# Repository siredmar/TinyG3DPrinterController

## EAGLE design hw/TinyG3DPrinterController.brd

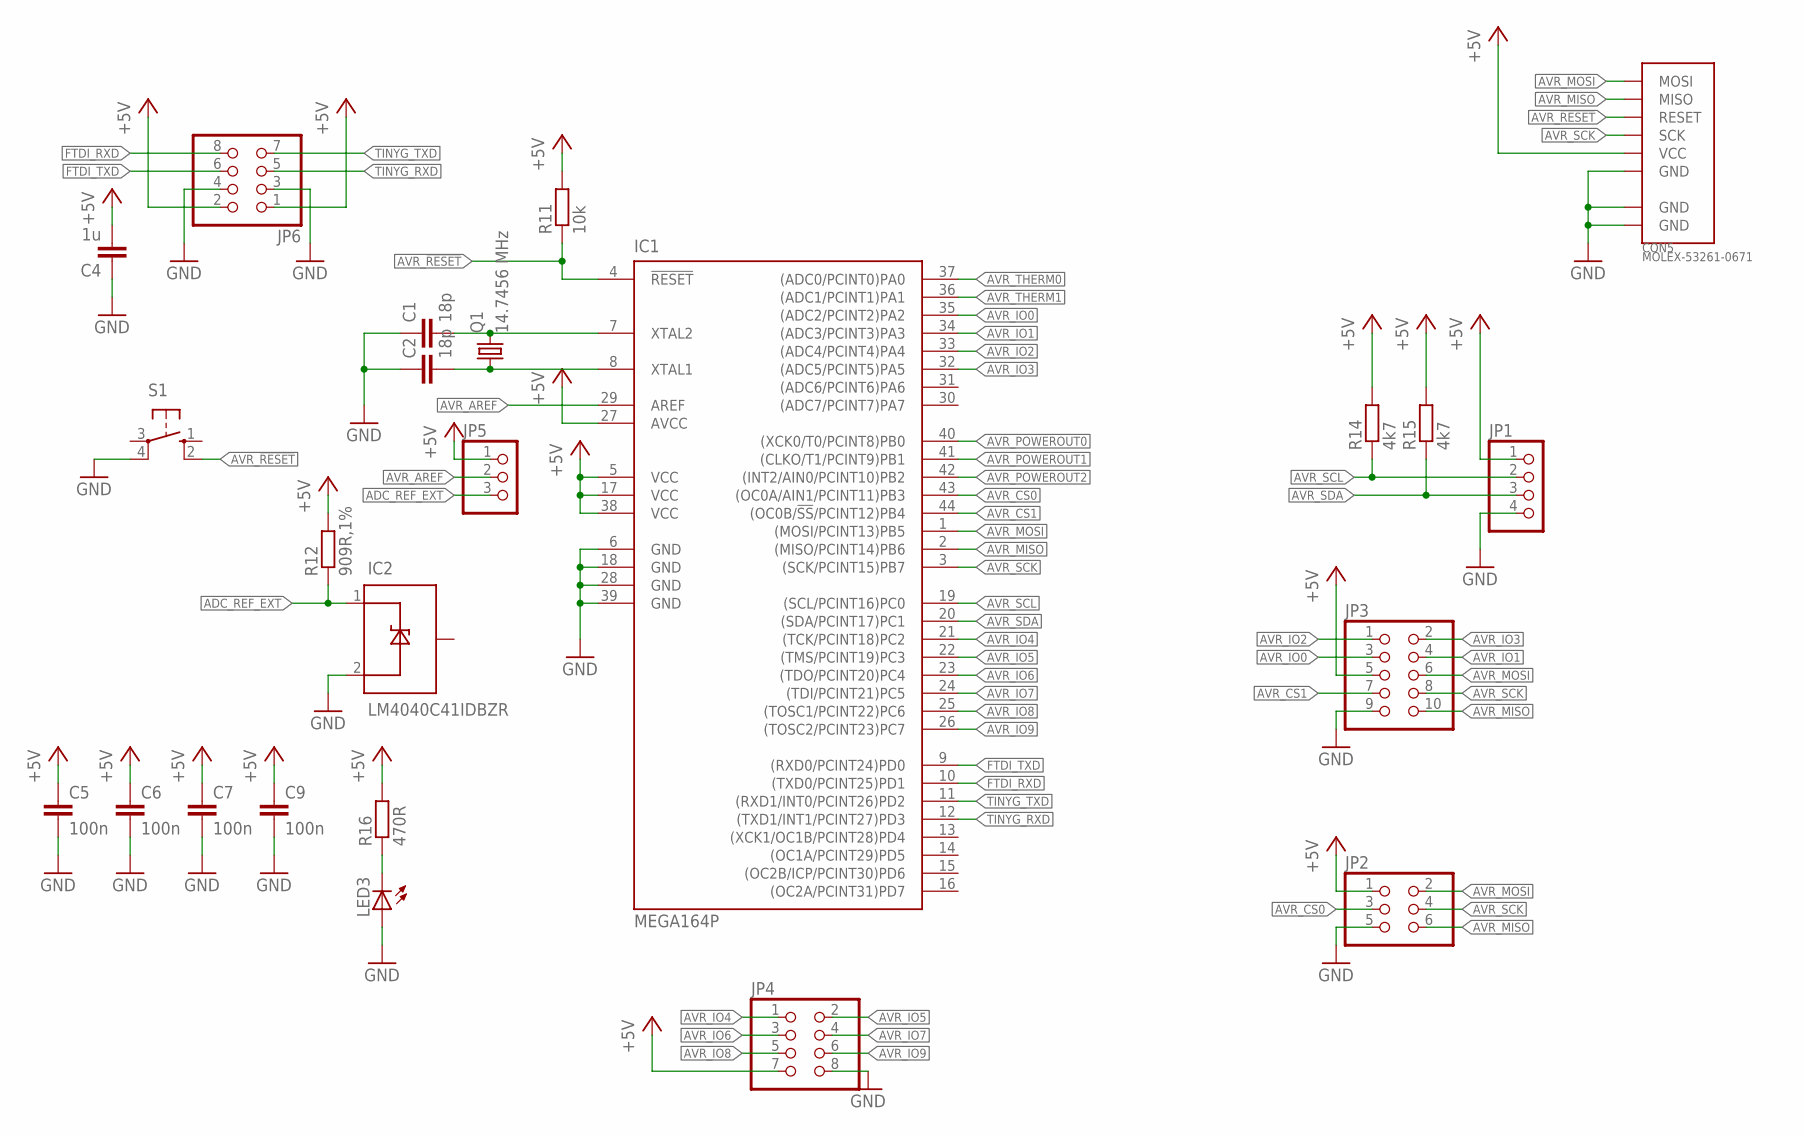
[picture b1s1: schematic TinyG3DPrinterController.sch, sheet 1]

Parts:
C1, C2: 18p; C0603K
C4: 1u; C1206K
C5, C6, C7, C9: 100n; C0603K
CON5: MOLEX-53261-0671
IC1: MEGA164P; TQFP44
IC2: LM4040C41IDBZR; SOT-23-3
JP1: PINHD-1X4; 1X04
JP2: PINHD-2X3; 2X03
JP3: PINHD-2X5; 2X05
JP4, JP6: PINHD-2X4; 2X04
JP5: PINHD-1X3; 1X03
LED3: LEDCHIP-LED0805; CHIP-LED0805
Q1: 14.7456 MHz; CRYSTAL_2P_5MMX3.2MM
R11: 10k; R0603
R12: 909R,1%; R0603
R14, R15: 4k7; R0603
R16: 470R; R0603
S1: 10-XX; B3F-10XX

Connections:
+5V: C4.2, C5.1, C6.1, C7.1, C9.1, CON5.5 (VCC), IC1.5 (VCC), IC1.17 (VCC), IC1.27 (AVCC), IC1.38 (VCC), JP1.1, JP2.1, JP3.5, JP4.7, JP5.1, JP6.1, JP6.2, R11.2, R12.2, R14.2, R15.2, R16.2; also elsewhere on the board
ADC_REF_EXT: IC2.1, JP5.3, R12.1
AVR_!RESET: CON5.3 (RESET), IC1.4 (!RESET), R11.1, S1.2 (S1)
AVR_AREF: IC1.29 (AREF), JP5.2
AVR_CS0: IC1.43 ((OC0A/AIN1/PCINT11)PB3), JP2.3
AVR_CS1: IC1.44 ((OC0B/!SS!/PCINT12)PB4), JP3.7
AVR_IO0: IC1.35 ((ADC2/PCINT2)PA2), JP3.3
AVR_IO1: IC1.34 ((ADC3/PCINT3)PA3), JP3.4
AVR_IO2: IC1.33 ((ADC4/PCINT4)PA4), JP3.1
AVR_IO3: IC1.32 ((ADC5/PCINT5)PA5), JP3.2
AVR_IO4: IC1.21 ((TCK/PCINT18)PC2), JP4.1
AVR_IO5: IC1.22 ((TMS/PCINT19)PC3), JP4.2
AVR_IO6: IC1.23 ((TDO/PCINT20)PC4), JP4.3
AVR_IO7: IC1.24 ((TDI/PCINT21)PC5), JP4.4
AVR_IO8: IC1.25 ((TOSC1/PCINT22)PC6), JP4.5
AVR_IO9: IC1.26 ((TOSC2/PCINT23)PC7), JP4.6
AVR_MISO: CON5.2 (MISO), IC1.2 ((MISO/PCINT14)PB6), JP2.6, JP3.10
AVR_MOSI: CON5.1 (MOSI), IC1.1 ((MOSI/PCINT13)PB5), JP2.2, JP3.6
AVR_POWEROUT0: IC1.40 ((XCK0/T0/PCINT8)PB0); also elsewhere on the board
AVR_POWEROUT1: IC1.41 ((CLKO/T1/PCINT9)PB1); also elsewhere on the board
AVR_POWEROUT2: IC1.42 ((INT2/AIN0/PCINT10)PB2); also elsewhere on the board
AVR_SCK: CON5.4 (SCK), IC1.3 ((SCK/PCINT15)PB7), JP2.4, JP3.8
AVR_SCL: IC1.19 ((SCL/PCINT16)PC0), JP1.2, R14.1
AVR_SDA: IC1.20 ((SDA/PCINT17)PC1), JP1.3, R15.1
AVR_THERM0: IC1.37 ((ADC0/PCINT0)PA0); also elsewhere on the board
AVR_THERM1: IC1.36 ((ADC1/PCINT1)PA1); also elsewhere on the board
FTDI_RXD: IC1.10 ((TXD0/PCINT25)PD1), JP6.8
FTDI_TXD: IC1.9 ((RXD0/PCINT24)PD0), JP6.6
GND: C1.1, C2.1, C4.1, C5.2, C6.2, C7.2, C9.2, CON5.6 (GND), CON5.GND@1 (GND), CON5.GND@2 (GND), IC1.6 (GND), IC1.18 (GND), IC1.28 (GND), IC1.39 (GND), IC2.2, JP1.4, JP2.5, JP3.9, JP4.8, JP6.3, JP6.4, LED3.A, S1.4 (P1); also elsewhere on the board
unnamed: C1.2, IC1.7 (XTAL2), Q1.P$2 (2)
unnamed: C2.2, IC1.8 (XTAL1), Q1.P$1 (1)
unnamed: LED3.C, R16.1
TINYG_RXD: IC1.12 ((TXD1/INT1/PCINT27)PD3), JP6.5
TINYG_TXD: IC1.11 ((RXD1/INT0/PCINT26)PD2), JP6.7

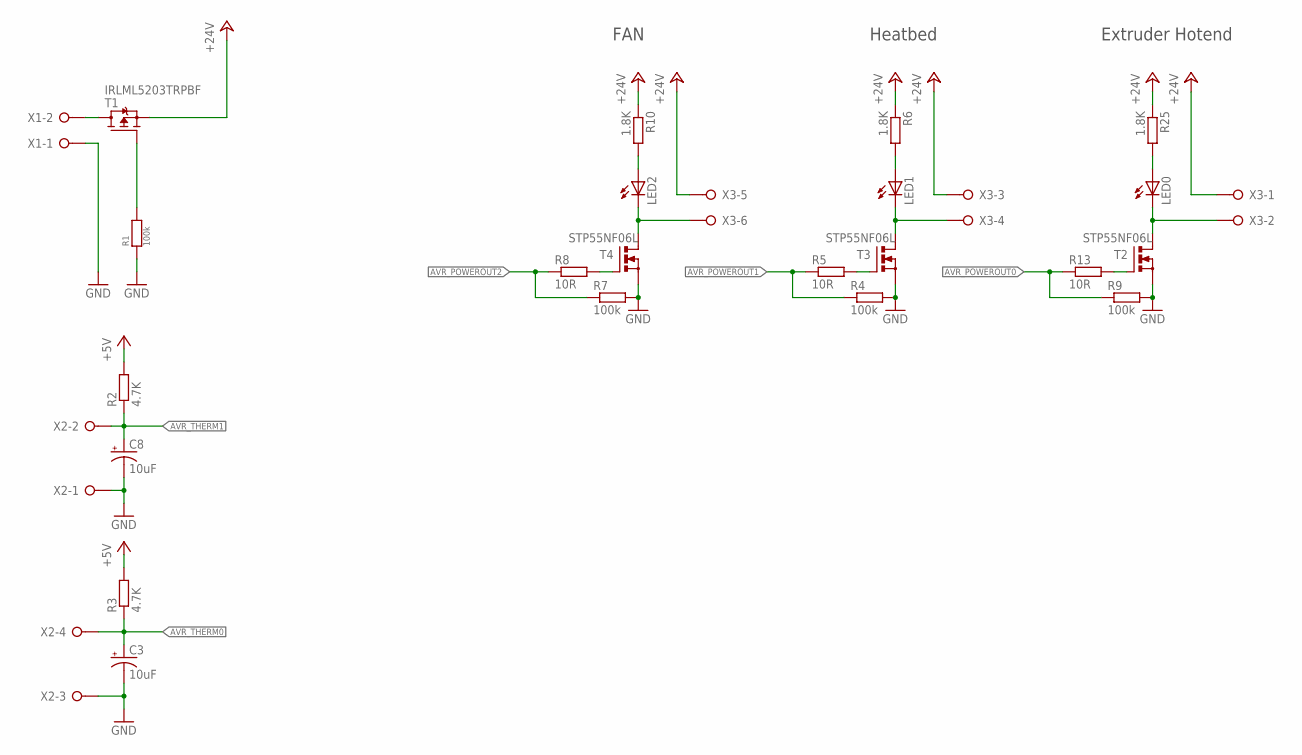
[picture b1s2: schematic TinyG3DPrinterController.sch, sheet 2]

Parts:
C3, C8: 10uF; 153CLV-0405
LED0, LED1, LED2: LEDCHIP-LED0805; CHIP-LED0805
R1, R4, R7, R9: 100k; R0603
R2, R3: 4.7K; R0603
R5, R8, R13: 10R; R0603
R6, R10, R25: 1.8K; R0603
T1: IRLML5203TRPBF; SOT23
T2, T3, T4: STP55NF06L; TO220BV
X1: W237-02P; W237-132
X2: W237-04P; W237-4P
X3: W237-06P; W237-6P

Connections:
+5V: R2.2, R3.2; also elsewhere on the board
+24V: R6.1, R10.1, R25.1, T1.2 (S), X3.1, X3.3, X3.5
AVR_POWEROUT0: R9.1, R13.1; also elsewhere on the board
AVR_POWEROUT1: R4.1, R5.1; also elsewhere on the board
AVR_POWEROUT2: R7.1, R8.1; also elsewhere on the board
AVR_THERM0: C3.+, R3.1, X2.4; also elsewhere on the board
AVR_THERM1: C8.+, R2.1, X2.2; also elsewhere on the board
GND: C3.-, C8.-, R1.1, R4.2, R7.2, R9.2, T2.S, T3.S, T4.S, X1.1, X2.1, X2.3; also elsewhere on the board
unnamed: R1.2, T1.1 (G)
unnamed: T1.3 (D), X1.2
unnamed: LED0.C, T2.D, X3.2
unnamed: R5.2, T3.G
unnamed: LED1.A, R6.2
unnamed: LED1.C, T3.D, X3.4
unnamed: R8.2, T4.G
unnamed: LED2.A, R10.2
unnamed: LED2.C, T4.D, X3.6
unnamed: R13.2, T2.G
unnamed: LED0.A, R25.2

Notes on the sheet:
Extruder Hotend
Heatbed
FAN

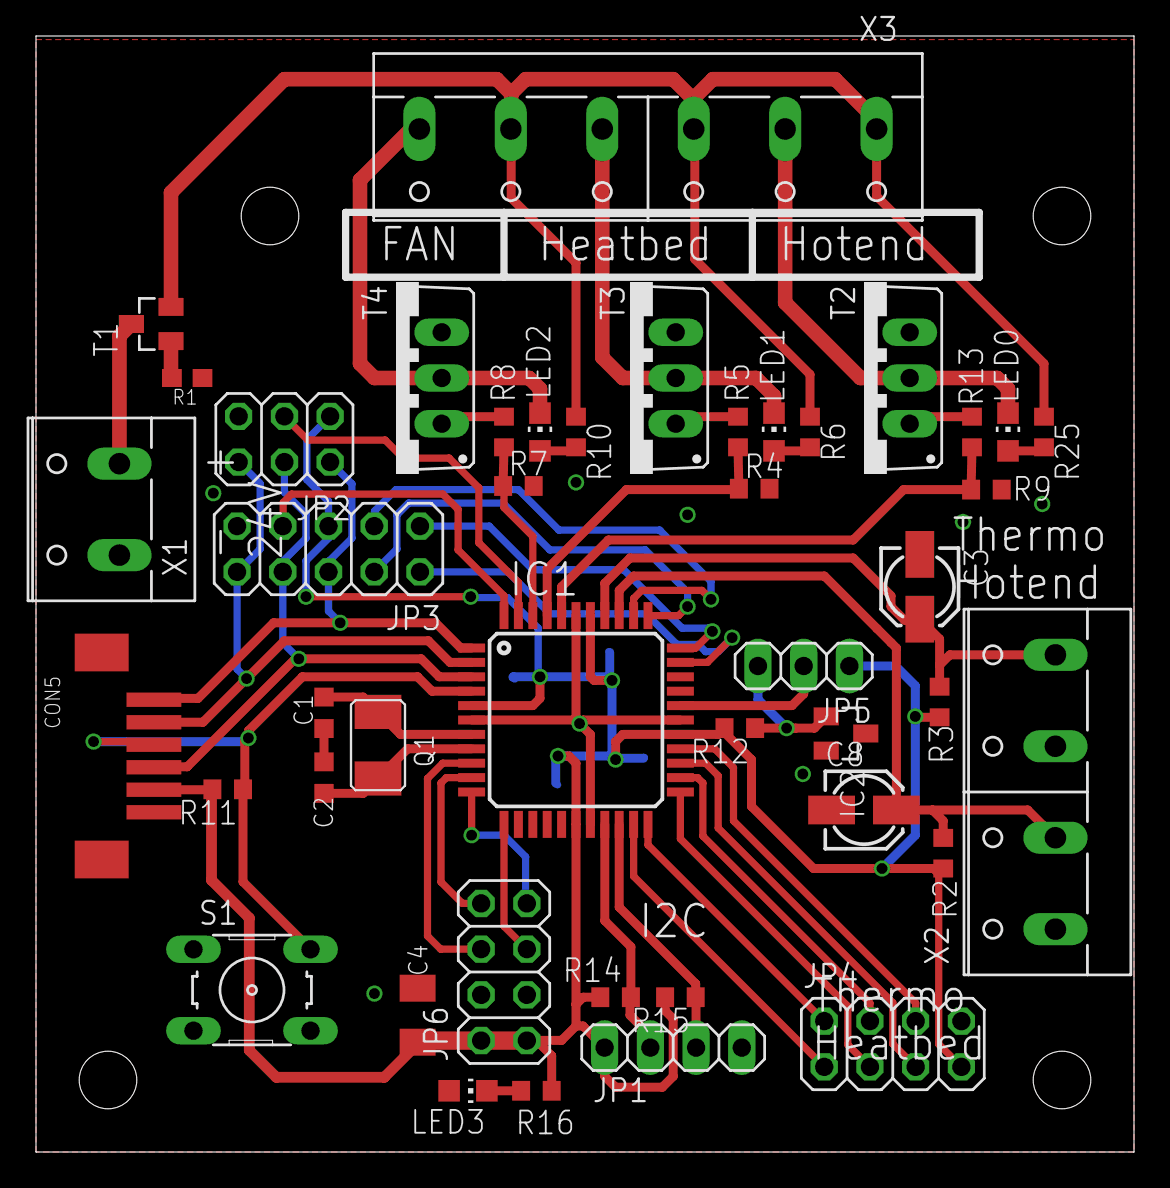
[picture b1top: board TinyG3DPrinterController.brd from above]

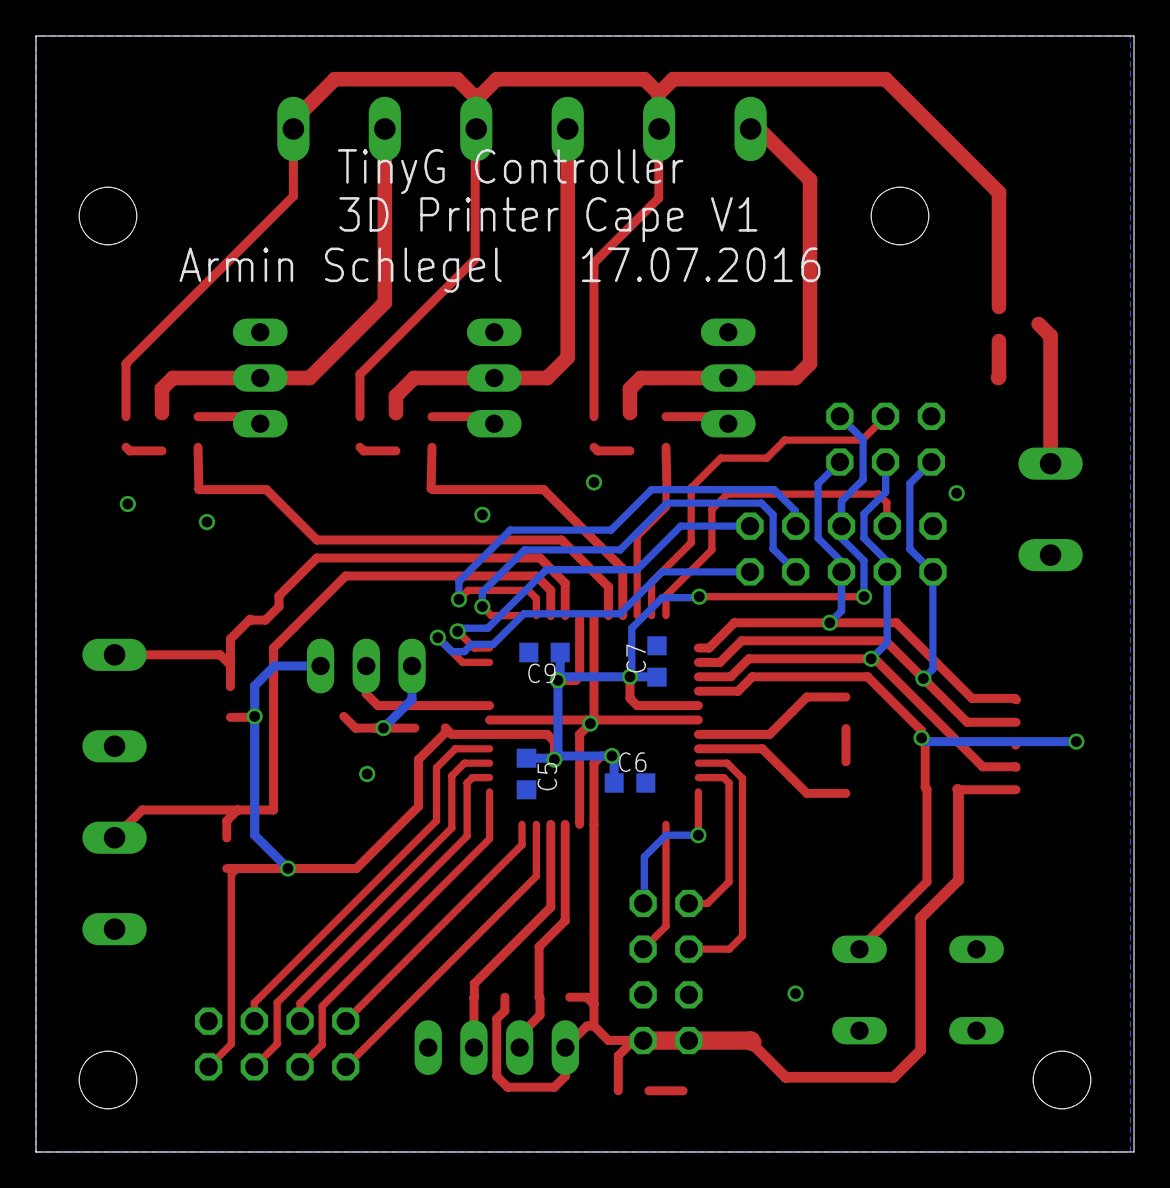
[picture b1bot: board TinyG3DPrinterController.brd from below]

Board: 2 copper layers, 61.0 x 62.0 mm, 48 parts (4 on the bottom side), 46 nets.

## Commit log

2016-07-03 First version of cape
2016-07-17 Adapted sch and brd files
